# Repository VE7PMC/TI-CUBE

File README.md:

# The TI CUBE

The `TI CUBE` is an open-source homebrew microcomputer project I designed around the Texas Instruments TMS 9900 microprocessor and its associated peripheral devices.

In its basic form the `TI CUBE` supports communications through two serial ports and has 32 KiB of ROM and 32 KiB of RAM for code and data storage. It also supports FM sound playback using the YM3812 OPL2 FM synthesis IC. **This even allows it to play Doom!**

\* of course it can't "play" Doom in the sense of rendering 3D video! [But it can *play back* the Doom music using the YM3812 FM synthesizer.](https://www.youtube.com/watch?v=pIbxxHVAydw)

# Why the TMS 9900?

The [TMS 9900 microprocessor was relatively advanced for its time (released in 1976)](https://www.cpushack.com/2015/02/05/ti-tms9900sbp9900-accidental-success/) and is essentially a single-chip version of TI's 990 series of 16-bit minicomputers from the 1970s. The TMS 9900 is considered one of the first true 16-bit microprocessors with a full 16-bit external data bus. This was allowed by the use of rather unconventional 64-pin DIP package. The address bus uses 15 bits, but since all memory accesses are 16-bits wide, this provides a 64 KiB address space (32 K of 16 bit words). The most unique feature of the TMS 9900 is that it had no internal registers, other than the program counter (PC), workspace pointer (WP), and status register (SR) - all 16-bits wide. Instead of internal registers, the WP pointed to a region in external memory where 16 "registers" were stored in sequential memory addresses. Adjusting the WP allowed for very fast context switching by pointing to a different set of "registers". This capability was used in TI 990 minicomputers to support multiuser computing.

The elegance of the internal AND external 16-bit data bus (unlike the crippled Intel 8088 CPU used in the first IBM PC), the quirkiness of its memory-based registers, and its unique serial-based I/O CRU interface make this chip a fascinating way to explore early microcomputer technology and its capabilities.

Finally, the project was greatly inspired by [Usagi Electric](https://www.youtube.com/@UsagiElectric)'s ongoing homebrew computer project based on the TMS 9900 CPU. I had a spare TMS 9900 IC that I removed from a TI-99/4A several decades ago(!), and figured this was a good way to put it to use. 

# Design Philosophy

The following principles guided my development of this homebrew project. The list is roughly in order of priority (highest is first).

1. **No 8-bit data buses!** The TMS 9900 microprocessor is fundamentally a 16-bit design descendent from TI's 990 series of 16-bit minicomputers and I wanted to honour this ancestry as much as possible. I find address/data bus muxing/demuxing complex and inelegant. Yes, the TMS 9900 isn't the fastest of the TMS 99xx series of microprocessors, but it's the only one that supports an *external* 16-bit data bus interface.

2. **Modularity.** Just like a minicomputer which would typically have a backplane populated with multiple cards, the `TI CUBE` uses a similar philosophy with three basic cards: 
   * CPU card (with clock and interrupt control)
   * Memory card (holding the RAM and ROM)
   * Serial port interface card (equipped with two serial chips driving two EIA-232C compatible ports). 
  
   All cards plug into a backplane using 72-pin header connectors. Any card can go in any slot, and multiple cards (e.g., multiple serial interface cards) are supported. Additional backplanes can also be daisy-chained to support additional card slots.

3. **Board size.** Constraining the board size to 100 x 100 mm (4 x 4 in) allows ordering PCBs using the [JLCPCB](https://jlcpcb.com) or [PCBWAY](https://pcbway.com) prototyping services (personally, I have had great experience with JLCPCB). This significantly reduces the cost of individual boards (approximately $2 per board). The physical construction also gives the `TI CUBE` its name: four 100 x 100 mm vertical cards plugged into a horizontal four-slot 100 x 100 mm backplane.

   Interestingly, these dimensions are similar to those used by [CubeSat](https://en.wikipedia.org/wiki/CubeSat) modules. Perhaps a `TI CUBE` will someday get launched into orbit as the most underpowered satellite ever.

5. **Simplicity.** I subscribe to the [Earl Muntz](https://en.wikipedia.org/wiki/Muntzing) philosophy. As such, the `TI CUBE` design uses the minimum required amount of components to accomplish its function. Random logic (i.e., TTL gates and decoders) is complex and consumes significant board space. Instead, I prefer to use simple and standard PLD devices like the ubiquitous 16V8, which does everything needed in one chip. This also allows easily reconfigurability simply by reprogramming the PLD.

   There are  no address or data buffers in the `TI CUBE`, but the small size combined with the use of four-layer PCBs keeps the digital signals clean; my builds have demonstrated excellent reliablity and performance. 

6. **Period correctness.** Primarily this means use of only through-hole components and no surface mount devices (SMD). I don't mind SMD as such, but through-hole is still easier to assemble and is more consistent with 70s/80s computers. I have violated the period-correctness rule in number of other places (e.g., use of PLDs instead of random logic, larger memory ICs compared to what was available in the 70s and early 80s), so this one is more a [guideline than an actual rule](https://www.youtube.com/watch?v=omjnIeLIzJc&t=13s). 😉

7. **Use of TMS 9900 family peripherals.** The TMS 9900 has a unique serial-oriented I/O bus: the "CRU" (communications-register unit). While there is a plethora of external I/O devices that could be memory mapped, I wanted the `TI CUBE` to remain consistent with the TMS 9900 ecosystem through the used of CRU-based I/O where possible. Currently, this includes the TMS 9901 programmable systems interface (PSI) and the TMS 9902 asynchronous communications controller (ACC). 
   
8. **Compatibility.** I designed the `TI CUBE` to be generally compatible with other TMS 9900-based systems. One excellent example is [Stuart Connor's TMS 9900 breadboard/PCB system](http://www.stuartconner.me.uk/tms9900_breadboard/tms9900_breadboard.htm). In fact, the binary files he provides can be downloaded, burned to EPROMs, and used directly in the `TI CUBE`. This includes the TIBUG and EVMBUG monitors and Cortex BASIC which work right out of the box!

# Folders

## [KiCad/](KiCad/README.md)

The complete schematic and PCB design files in KiCad format. The schematics are also available in PDF format.

## [PLD configs/](PLD%20configs/README.md)

Files containing the address decoding logic for the various peripherals.

## [firmware/](firmware/README.md)

Binary files developed by Stuart Connor ready for burning to EPROMs. These contain TIBUG, EVMBUG, and Cortext BASIC.

## [hardware/](hardware/README.md)

The bill of materials and suggestions for acquiring the necessary components.

## [gerbers/](gerbers/README.md)

PCB design files ready for uploaded to your favourite PCB manufacturing house.

# Future Expansion/Ideas

This [file](FUTURE.md) contains my current thoughts on future expansions and/or design modifications.

# References

* [TI 9900 Family Systems Design and Data Book](https://www.bitsavers.org/components/ti/TMS9900/1978_TI_9900_Family_Systems_Design_and_Data_Book_1ed.pdf)
* [TMS 9900 Microprocessor Data Manual](https://datasheets.chipdb.org/TI/9900/TMS9900_DataManual.pdf)
* [The TI-99/4A Tech Pages](https://www.unige.ch/medecine/nouspikel/ti99/titechpages.htm)
* [TI TMS9900/SBP9900: Accidental Success](https://www.cpushack.com/2015/02/05/ti-tms9900sbp9900-accidental-success/)
* [The Inside Story of Texas Instruments’ Biggest Blunder: The TMS9900 Microprocessor](https://spectrum.ieee.org/the-inside-story-of-texas-instruments-biggest-blunder-the-tms9900-microprocessor)

# Acknowledgements

The following are excellent resources from other experimenters with the TMS 9900:

* [Usagi Electric's](https://www.youtube.com/@UsagiElectric) awesome YouTube channel.
* [Stuart Conner's Home Page](http://www.stuartconner.me.uk/) contains very helpful hardware designs and software files which I have referenced in the `TI CUBE` design.
* [POWERTRAN Cortex](http://powertrancortex.com/index.html) contains source code for Cortex BASIC which can be modified to run on the `TI CUBE`.

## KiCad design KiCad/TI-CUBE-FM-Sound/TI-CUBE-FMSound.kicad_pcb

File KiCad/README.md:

# TI Cube schematics and PCB design files

These folders contain the schematic and PCB design files for the four boards and backplane in KiCad 9.0.7 format.

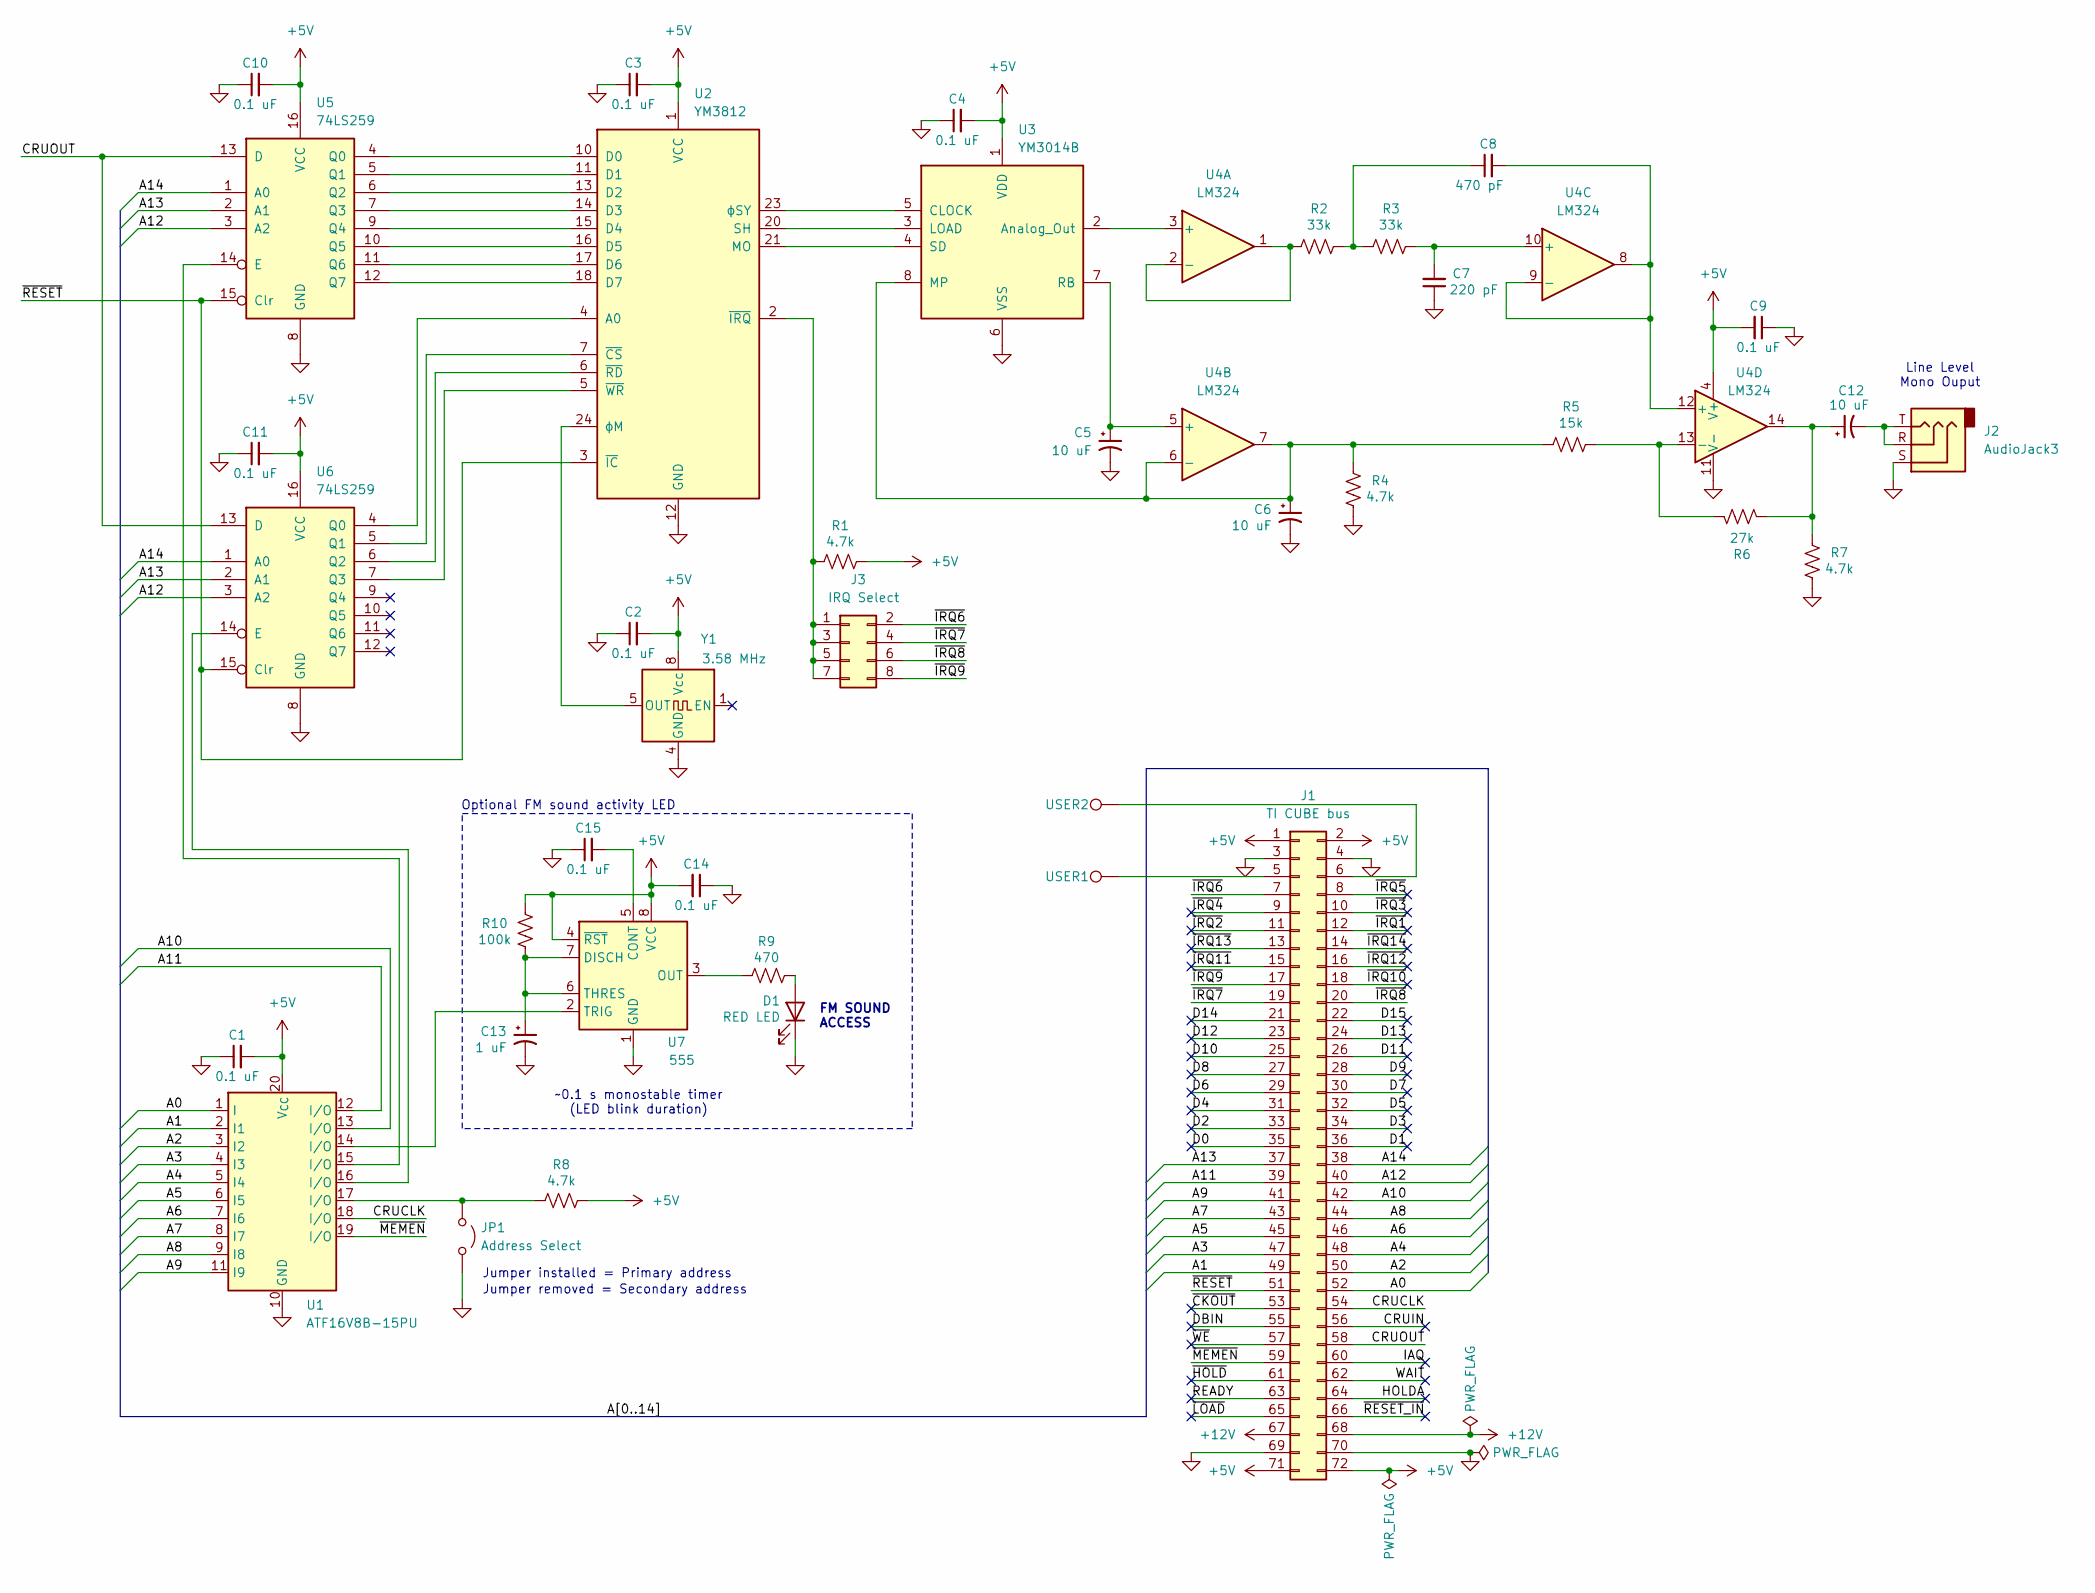
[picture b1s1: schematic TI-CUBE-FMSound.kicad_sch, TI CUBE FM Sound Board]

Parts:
C1, C2, C3, C4, C9, C10, C11, C14, C15: 0.1 uF; C_Ceramic_Cap_P2.50mm
C5, C6, C12: 10 uF; CP_Radial_D5.0mm_P2.50mm
C7: 220 pF; C_Ceramic_Cap_P2.50mm
C8: 470 pF; C_Ceramic_Cap_P2.50mm
C13: 1 uF; CP_Radial_D5.0mm_P2.50mm
D1: RED LED; LED_D3.0mm_Horizontal_O1.27mm_Z2.0mm
J1: TI CUBE bus; PinHeader_2x36_P2.54mm_Horizontal
J2: AudioJack3; Jack_3.5mm_CUI_SJ1-3513N_Horizontal
J3: IRQ Select; PinHeader_2x04_P2.54mm_Vertical
JP1: Address Select; PinHeader_1x02_P2.54mm_Vertical
R1, R4, R7, R8: 4.7k; R_Axial_DIN0207_L6.3mm_D2.5mm_P10.16mm_Horizontal
R2, R3: 33k; R_Axial_DIN0207_L6.3mm_D2.5mm_P10.16mm_Horizontal
R5: 15k; R_Axial_DIN0207_L6.3mm_D2.5mm_P10.16mm_Horizontal
R6: 27k; R_Axial_DIN0207_L6.3mm_D2.5mm_P10.16mm_Horizontal
R9: 470; R_Axial_DIN0207_L6.3mm_D2.5mm_P10.16mm_Horizontal
R10: 100k; R_Axial_DIN0207_L6.3mm_D2.5mm_P10.16mm_Horizontal
U1: ATF16V8B-15PU; DIP-20_W7.62mm
U2: YM3812; DIP-24_W15.24mm
U3: YM3014B; DIP-8_W7.62mm
U4: LM324; DIP-14_W7.62mm
U5, U6: 74LS259; DIP-16_W7.62mm
U7: 555; DIP-8_W7.62mm
USER1: USER1; TestPoint_THTPad_D1.5mm_Drill0.7mm
USER2: USER2; TestPoint_THTPad_D1.5mm_Drill0.7mm
Y1: 3.58 MHz; Oscillator_DIP-8

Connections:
+5V: C1.2, C2.2, C3.2, C4.2, C9.2, C10.2, C11.2, C14.2, J1.1, J1.2, J1.71, J1.72, R1.1, R8.1, R10.1, U1.20 (V_{CC}), U2.1 (VCC), U3.1 (VDD), U4.4 (V+), U5.16 (VCC), U6.16 (VCC), U7.4 (~RST), U7.8 (VCC), Y1.8 (Vcc)
+12V: J1.67, J1.68
/A0: J1.52, U1.1 (I)
/A1: J1.49, U1.2 (I1)
/A2: J1.50, U1.3 (I2)
/A3: J1.47, U1.4 (I3)
/A4: J1.48, U1.5 (I4)
/A5: J1.45, U1.6 (I5)
/A6: J1.46, U1.7 (I6)
/A7: J1.43, U1.8 (I7)
/A8: J1.44, U1.9 (I8)
/A9: J1.41, U1.11 (I9)
/A10: J1.42, U1.13 (I/O)
/A11: J1.39, U1.12 (I/O)
/A12: J1.40, U5.3 (A2), U6.3 (A2)
/A13: J1.37, U5.2 (A1), U6.2 (A1)
/A14: J1.38, U5.1 (A0), U6.1 (A0)
/CRUCLK: J1.54, U1.18 (I/O)
/CRUIN: J1.56
/CRUOUT: J1.58, U5.13 (D), U6.13 (D)
/D0: J1.35
/D1: J1.36
/D2: J1.33
/D3: J1.34
/D4: J1.31
/D5: J1.32
/D6: J1.29
/D7: J1.30
/D8: J1.27
/D9: J1.28
/D10: J1.25
/D11: J1.26
/D12: J1.23
/D13: J1.24
/D14: J1.21
/D15: J1.22
/DBIN: J1.55
/HOLDA: J1.64
/IAQ: J1.60
/READY: J1.63
/WAIT: J1.62
/~CKOUT: J1.53
/~HOLD: J1.61
/~IRQ1: J1.12
/~IRQ2: J1.11
/~IRQ3: J1.10
/~IRQ4: J1.9
/~IRQ5: J1.8
/~IRQ6: J1.7, J3.2
/~IRQ7: J1.19, J3.4
/~IRQ8: J1.20, J3.6
/~IRQ9: J1.17, J3.8
/~IRQ10: J1.18
/~IRQ11: J1.15
/~IRQ12: J1.16
/~IRQ13: J1.13
/~IRQ14: J1.14
/~LOAD: J1.65
/~MEMEN: J1.59, U1.19 (I/O)
/~RESET_IN: J1.66
/~RESET: J1.51, U2.3 (~IC), U5.15 (Clr), U6.15 (Clr)
/~WE: J1.57
GND: C1.1, C2.1, C3.1, C4.1, C5.2, C6.2, C7.1, C9.1, C10.1, C11.1, C13.2, C14.1, C15.1, D1.1 (K), J1.3, J1.4, J1.69, J1.70, J2.S, JP1.2 (B), R4.1, R7.1, U1.10 (GND), U2.12 (GND), U3.6 (VSS), U4.11 (V-), U5.8 (GND), U6.8 (GND), U7.1 (GND), Y1.4 (GND)
unnamed: C8.1, R2.1, R3.2
unnamed: C12.1, R6.1, R7.2, U4.14
unnamed: C12.2, J2.R, J2.T
unnamed: D1.2 (A), R9.1
unnamed: J1.5, USER1.1
unnamed: J1.6, USER2.1
unnamed: J3.1, J3.3, J3.5, J3.7, R1.2, U2.2 (~IRQ)
unnamed: JP1.1 (A), R8.2, U1.17 (I/O)
unnamed: U2.4 (A0), U6.4 (Q0)
unnamed: U2.10 (D0), U5.4 (Q0)
unnamed: U2.11 (D1), U5.5 (Q1)
unnamed: U2.13 (D2), U5.6 (Q2)
unnamed: U2.14 (D3), U5.7 (Q3)
unnamed: U2.15 (D4), U5.9 (Q4)
unnamed: U2.16 (D5), U5.10 (Q5)
unnamed: U2.17 (D6), U5.11 (Q6)
unnamed: U2.18 (D7), U5.12 (Q7)
unnamed: U2.21 (MO), U3.4 (SD)
unnamed: U2.20 (SH), U3.3 (LOAD)
unnamed: U2.7 (~CS), U6.5 (Q1)
unnamed: U2.6 (~RD), U6.6 (Q2)
unnamed: U2.5 (~WR), U6.7 (Q3)
unnamed: U2.24 (ϕM), Y1.5 (OUT)
unnamed: U2.23 (ϕSY), U3.5 (CLOCK)
unnamed: U3.2 (Analog_Out), U4.3 (+)
unnamed: C6.1, R4.2, R5.2, U3.8 (MP), U4.6 (-), U4.7
unnamed: C5.1, U3.7 (RB), U4.5 (+)
unnamed: R2.2, U4.1, U4.2 (-)
unnamed: C7.2, R3.1, U4.10 (+)
unnamed: C8.2, U4.8, U4.9 (-), U4.12 (+)
unnamed: R5.1, R6.2, U4.13 (-)
unnamed: U1.15 (I/O), U5.14 (E)
unnamed: U1.16 (I/O), U6.14 (E)
unnamed: C15.2, U7.5 (CONT)
unnamed: C13.1, R10.2, U7.6 (THRES), U7.7 (DISCH)
unnamed: R9.2, U7.3 (OUT)
unnamed: U1.14 (I/O), U7.2 (TRIG)

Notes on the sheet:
Line Level Mono Ouput
Optional FM sound activity LED
Jumper removed = Secondary address
FM SOUND ACCESS
~0.1 s monostable timer (LED blink duration)
Jumper installed = Primary address

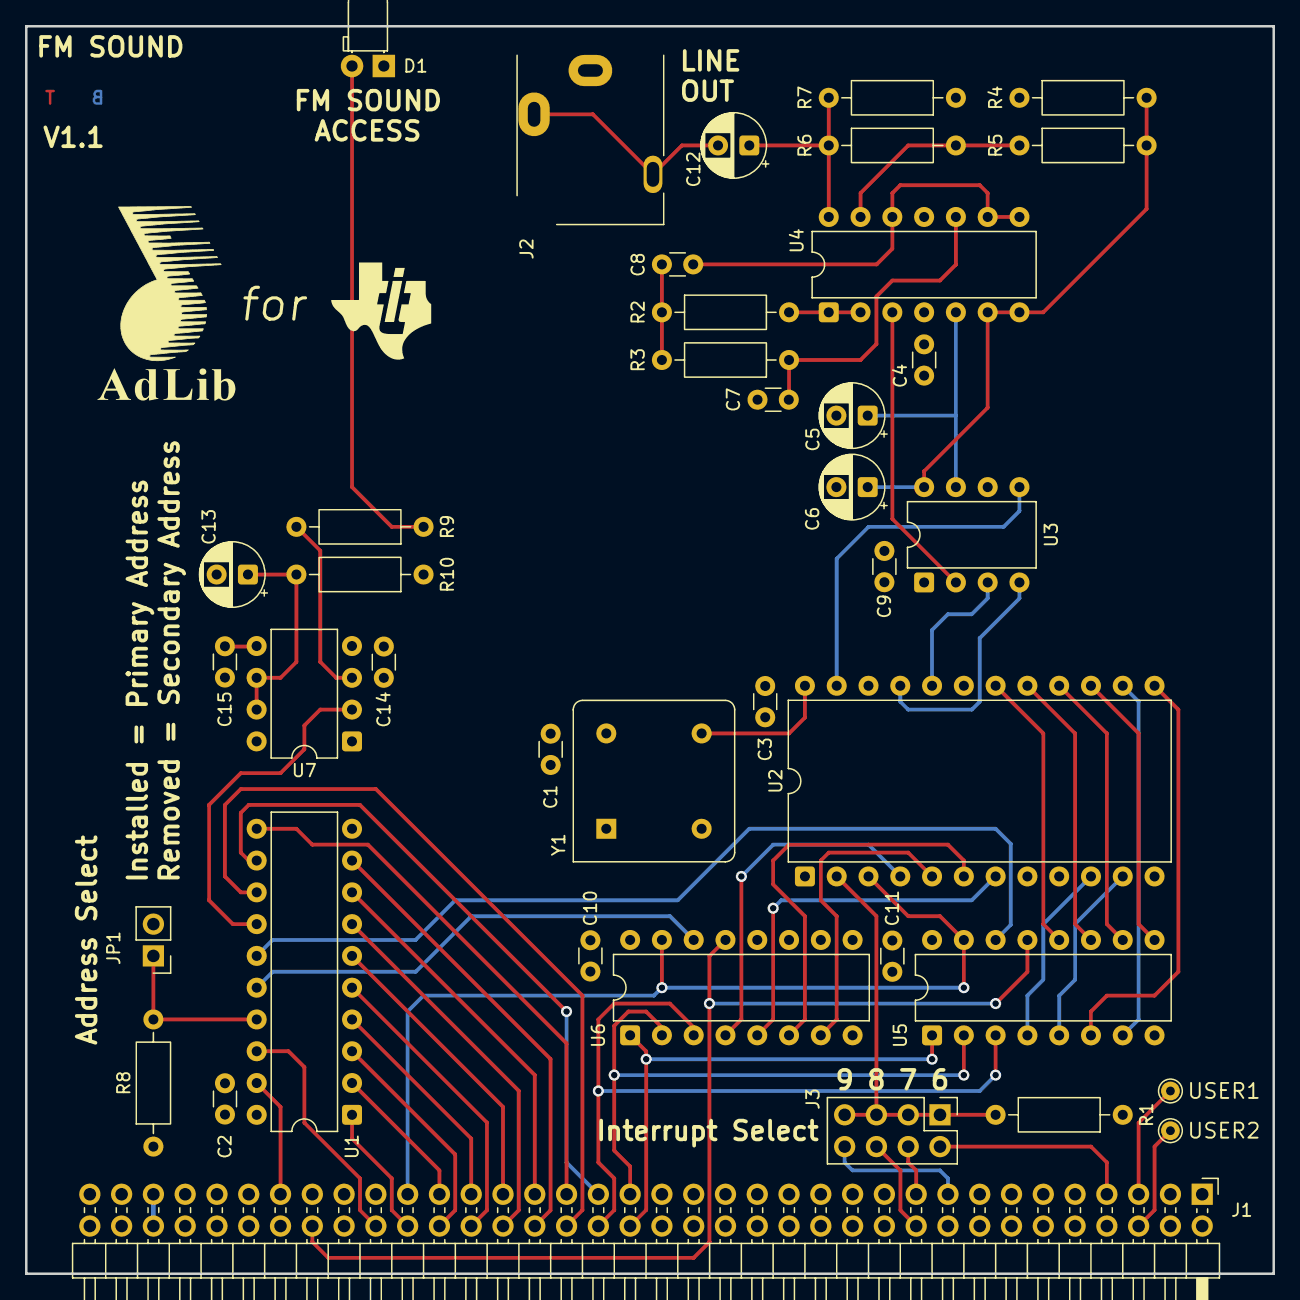
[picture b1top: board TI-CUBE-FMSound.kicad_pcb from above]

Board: 4 copper layers, 99.7 x 99.7 mm, 40 parts (0 on the bottom side), 63 nets.

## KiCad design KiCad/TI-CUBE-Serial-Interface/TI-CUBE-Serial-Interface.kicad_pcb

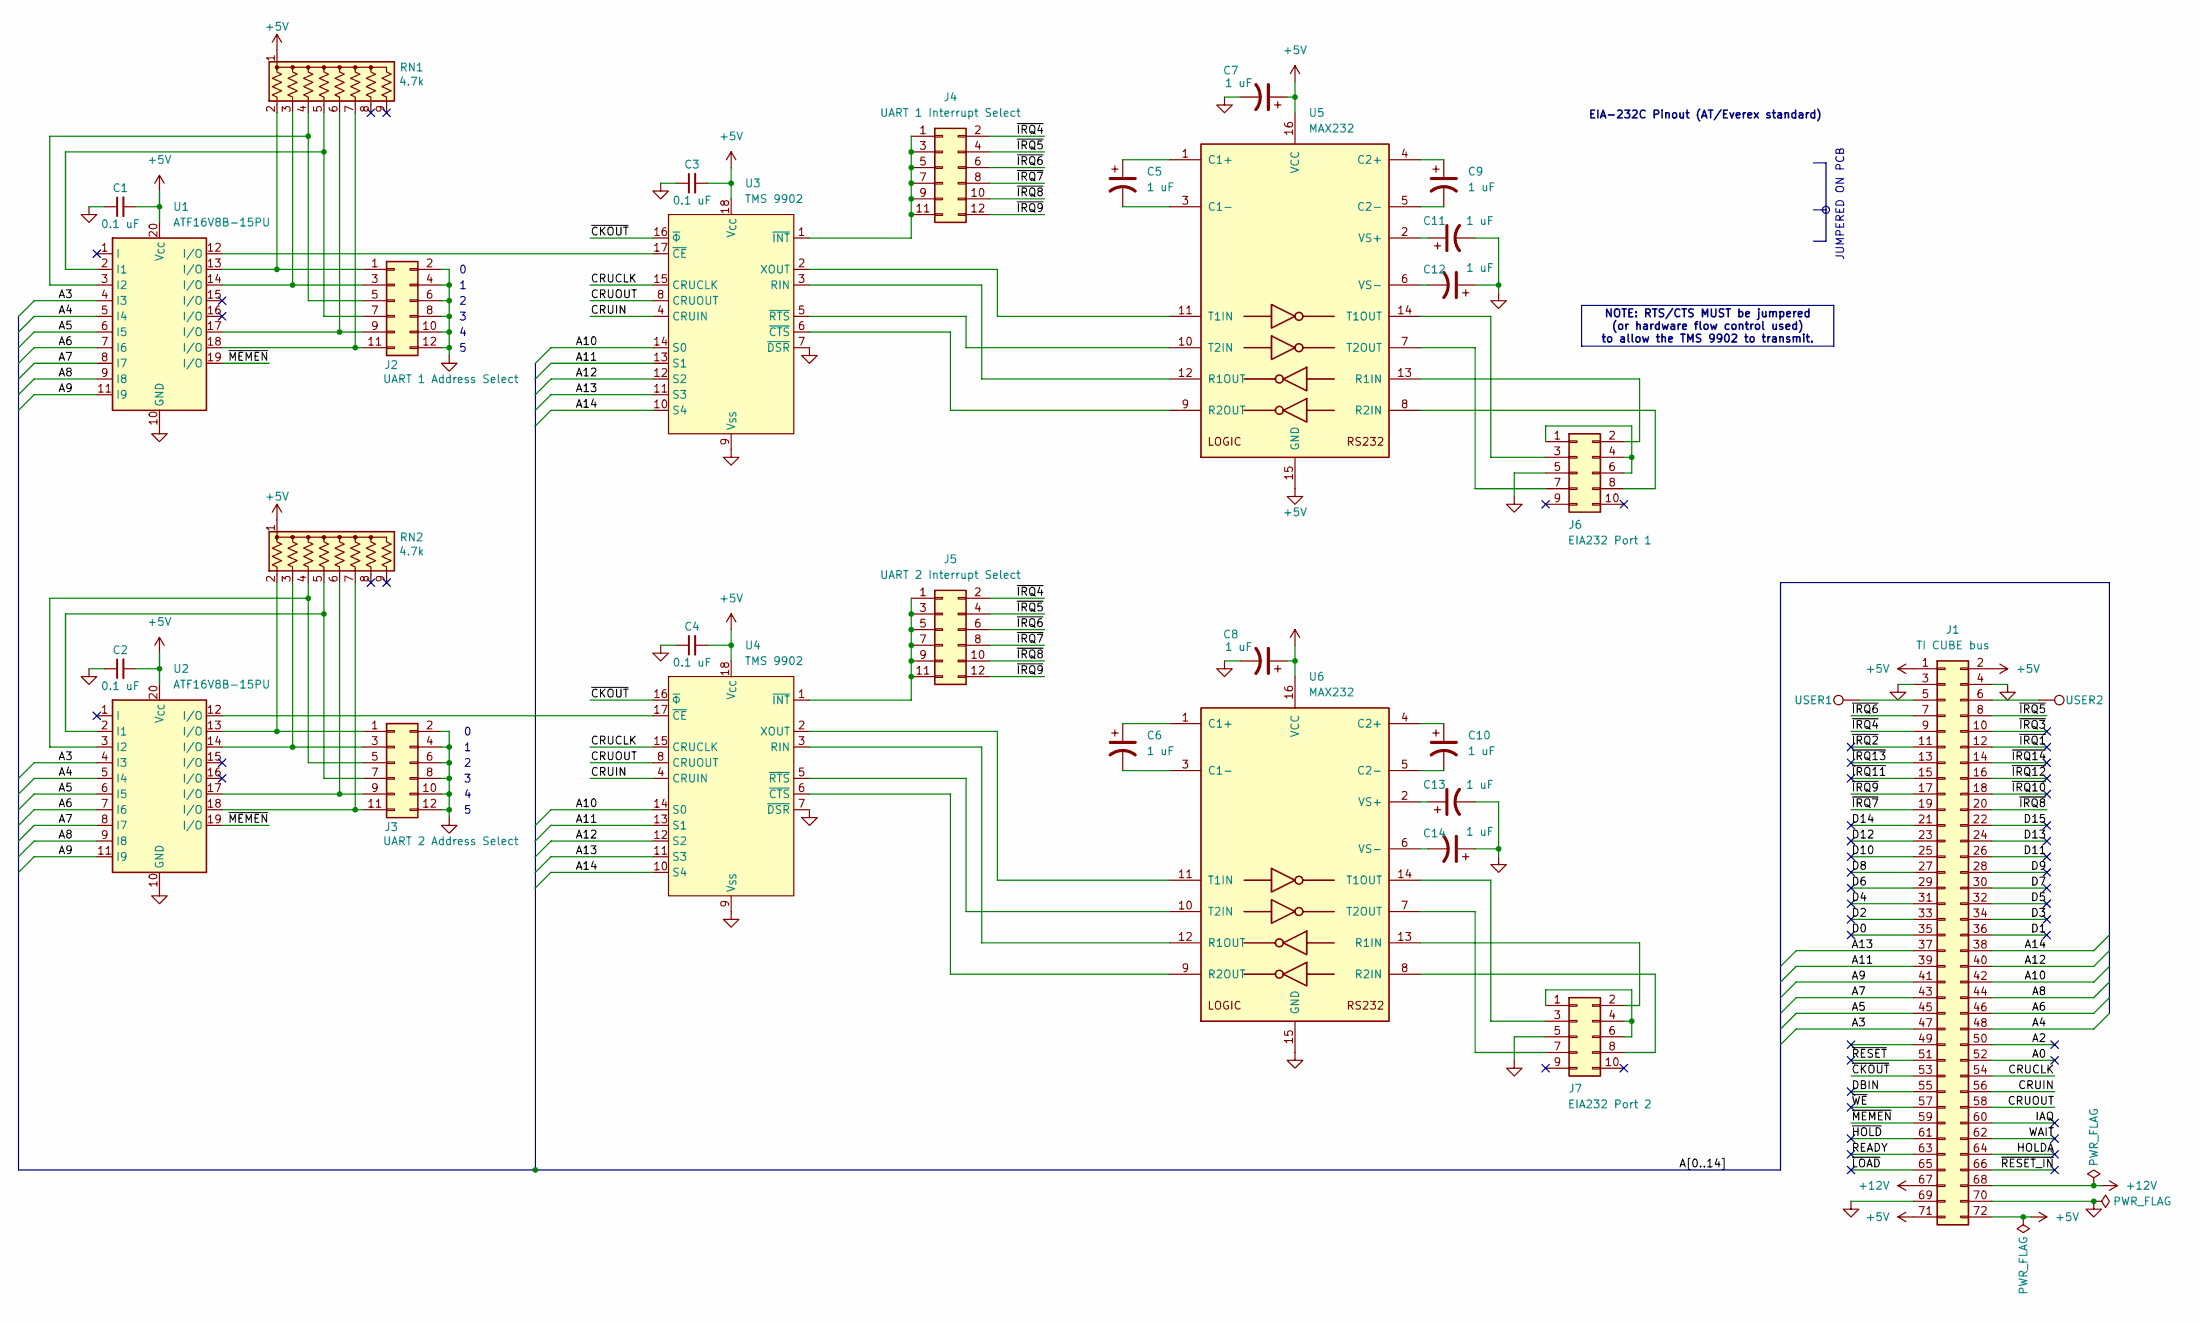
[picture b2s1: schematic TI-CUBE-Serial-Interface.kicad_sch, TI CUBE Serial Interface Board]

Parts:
C1, C2, C3, C4: 0.1 uF; C_Ceramic_Cap_P2.50mm
C5, C6, C7, C8, C9, C10, C11, C12, C13, C14: 1 uF; CP_Radial_D5.0mm_P2.50mm
J1: TI CUBE bus; PinHeader_2x36_P2.54mm_Horizontal
J2: UART 1 Address Select; PinHeader_2x06_P2.54mm_Vertical
J3: UART 2 Address Select; PinHeader_2x06_P2.54mm_Vertical
J4: UART 1 Interrupt Select; PinHeader_2x06_P2.54mm_Vertical
J5: UART 2 Interrupt Select; PinHeader_2x06_P2.54mm_Vertical
J6: EIA232 Port 1; PinHeader_2x05_P2.54mm_Horizontal
J7: EIA232 Port 2; PinHeader_2x05_P2.54mm_Horizontal
RN1, RN2: 4.7k; R_Array_SIP9
U1, U2: ATF16V8B-15PU; DIP-20_W7.62mm
U3, U4: TMS 9902; DIP-18_W7.62mm
U5, U6: MAX232; DIP-16_W7.62mm
USER1: USER2; TestPoint_THTPad_D1.5mm_Drill0.7mm
USER2: USER1; TestPoint_THTPad_D1.5mm_Drill0.7mm

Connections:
+5V: C1.2, C2.2, C3.2, C4.2, C7.1, C8.1, J1.1, J1.2, J1.71, J1.72, RN1.1 (common), RN2.1 (common), U1.20 (V_{CC}), U2.20 (V_{CC}), U3.18 (V_{CC}), U4.18 (V_{CC}), U5.16 (VCC), U6.16 (VCC)
+12V: J1.67, J1.68
/A0: J1.52
/A2: J1.50
/A3: J1.47, U1.4 (I3), U2.4 (I3)
/A4: J1.48, U1.5 (I4), U2.5 (I4)
/A5: J1.45, U1.6 (I5), U2.6 (I5)
/A6: J1.46, U1.7 (I6), U2.7 (I6)
/A7: J1.43, U1.8 (I7), U2.8 (I7)
/A8: J1.44, U1.9 (I8), U2.9 (I8)
/A9: J1.41, U1.11 (I9), U2.11 (I9)
/A10: J1.42, U3.14 (S0), U4.14 (S0)
/A11: J1.39, U3.13 (S1), U4.13 (S1)
/A12: J1.40, U3.12 (S2), U4.12 (S2)
/A13: J1.37, U3.11 (S3), U4.11 (S3)
/A14: J1.38, U3.10 (S4), U4.10 (S4)
/CRUCLK: J1.54, U3.15 (CRUCLK), U4.15 (CRUCLK)
/CRUIN: J1.56, U3.4 (CRUIN), U4.4 (CRUIN)
/CRUOUT: J1.58, U3.8 (CRUOUT), U4.8 (CRUOUT)
/D0: J1.35
/D1: J1.36
/D2: J1.33
/D3: J1.34
/D4: J1.31
/D5: J1.32
/D6: J1.29
/D7: J1.30
/D8: J1.27
/D9: J1.28
/D10: J1.25
/D11: J1.26
/D12: J1.23
/D13: J1.24
/D14: J1.21
/D15: J1.22
/DBIN: J1.55
/HOLDA: J1.64
/IAQ: J1.60
/READY: J1.63
/WAIT: J1.62
/~CKOUT: J1.53, U3.16 (~Φ), U4.16 (~Φ)
/~HOLD: J1.61
/~IRQ1: J1.12
/~IRQ2: J1.11
/~IRQ3: J1.10
/~IRQ4: J1.9, J4.2, J5.2
/~IRQ5: J1.8, J4.4, J5.4
/~IRQ6: J1.7, J4.6, J5.6
/~IRQ7: J1.19, J4.8, J5.8
/~IRQ8: J1.20, J4.10, J5.10
/~IRQ9: J1.17, J4.12, J5.12
/~IRQ10: J1.18
/~IRQ11: J1.15
/~IRQ12: J1.16
/~IRQ13: J1.13
/~IRQ14: J1.14
/~LOAD: J1.65
/~MEMEN: J1.59, U1.19 (I/O), U2.19 (I/O)
/~RESET_IN: J1.66
/~RESET: J1.51
/~WE: J1.57
GND: C1.1, C2.1, C3.1, C4.1, C7.2, C8.2, C11.2, C12.1, C13.2, C14.1, J1.3, J1.4, J1.69, J1.70, J2.2, J2.4, J2.6, J2.8, J2.10, J2.12, J3.2, J3.4, J3.6, J3.8, J3.10, J3.12, J6.5, J7.5, U1.10 (GND), U2.10 (GND), U3.7 (~DSR), U3.9 (V_{SS}), U4.7 (~DSR), U4.9 (V_{SS}), U5.15 (GND), U6.15 (GND)
unnamed: J1.5, USER2.1
unnamed: J1.6, USER1.1
unnamed: J2.1, RN1.2 (R1), U1.13 (I/O)
unnamed: J2.3, RN1.3 (R2), U1.14 (I/O)
unnamed: J2.5, RN1.4 (R3), U1.3 (I2)
unnamed: J2.7, RN1.5 (R4), U1.2 (I1)
unnamed: J2.9, RN1.6 (R5), U1.17 (I/O)
unnamed: J2.11, RN1.7 (R6), U1.18 (I/O)
unnamed: J3.1, RN2.2 (R1), U2.13 (I/O)
unnamed: J3.3, RN2.3 (R2), U2.14 (I/O)
unnamed: J3.5, RN2.4 (R3), U2.3 (I2)
unnamed: J3.7, RN2.5 (R4), U2.2 (I1)
unnamed: J3.9, RN2.6 (R5), U2.17 (I/O)
unnamed: J3.11, RN2.7 (R6), U2.18 (I/O)
unnamed: J4.1, J4.3, J4.5, J4.7, J4.9, J4.11, U3.1 (~INT)
unnamed: J5.1, J5.3, J5.5, J5.7, J5.9, J5.11, U4.1 (~INT)
unnamed: J6.1, J6.4, J6.6
unnamed: J6.2, U5.13 (R1IN)
unnamed: J6.3, U5.14 (T1OUT)
unnamed: J6.7, U5.7 (T2OUT)
unnamed: J6.8, U5.8 (R2IN)
unnamed: J7.1, J7.4, J7.6
unnamed: J7.2, U6.13 (R1IN)
unnamed: J7.3, U6.14 (T1OUT)
unnamed: J7.7, U6.7 (T2OUT)
unnamed: J7.8, U6.8 (R2IN)
unnamed: U3.3 (RIN), U5.12 (R1OUT)
unnamed: U3.2 (XOUT), U5.11 (T1IN)
unnamed: U1.12 (I/O), U3.17 (~CE)
unnamed: U3.6 (~CTS), U5.9 (R2OUT)
unnamed: U3.5 (~RTS), U5.10 (T2IN)
unnamed: U4.3 (RIN), U6.12 (R1OUT)
unnamed: U4.2 (XOUT), U6.11 (T1IN)
unnamed: U2.12 (I/O), U4.17 (~CE)
unnamed: U4.6 (~CTS), U6.9 (R2OUT)
unnamed: U4.5 (~RTS), U6.10 (T2IN)
unnamed: C5.1, U5.1 (C1+)
unnamed: C5.2, U5.3 (C1-)
unnamed: C9.1, U5.4 (C2+)
unnamed: C9.2, U5.5 (C2-)
unnamed: C11.1, U5.2 (VS+)
unnamed: C12.2, U5.6 (VS-)
unnamed: C6.1, U6.1 (C1+)
unnamed: C6.2, U6.3 (C1-)
unnamed: C10.1, U6.4 (C2+)
unnamed: C10.2, U6.5 (C2-)
unnamed: C13.1, U6.2 (VS+)
unnamed: C14.2, U6.6 (VS-)

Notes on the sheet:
JUMPERED ON PCB
EIA-232C Pinout (AT/Everex standard)
NOTE: RTS/CTS MUST be jumpered (or hardware flow control used) to allow the TMS 9902 to transmit.

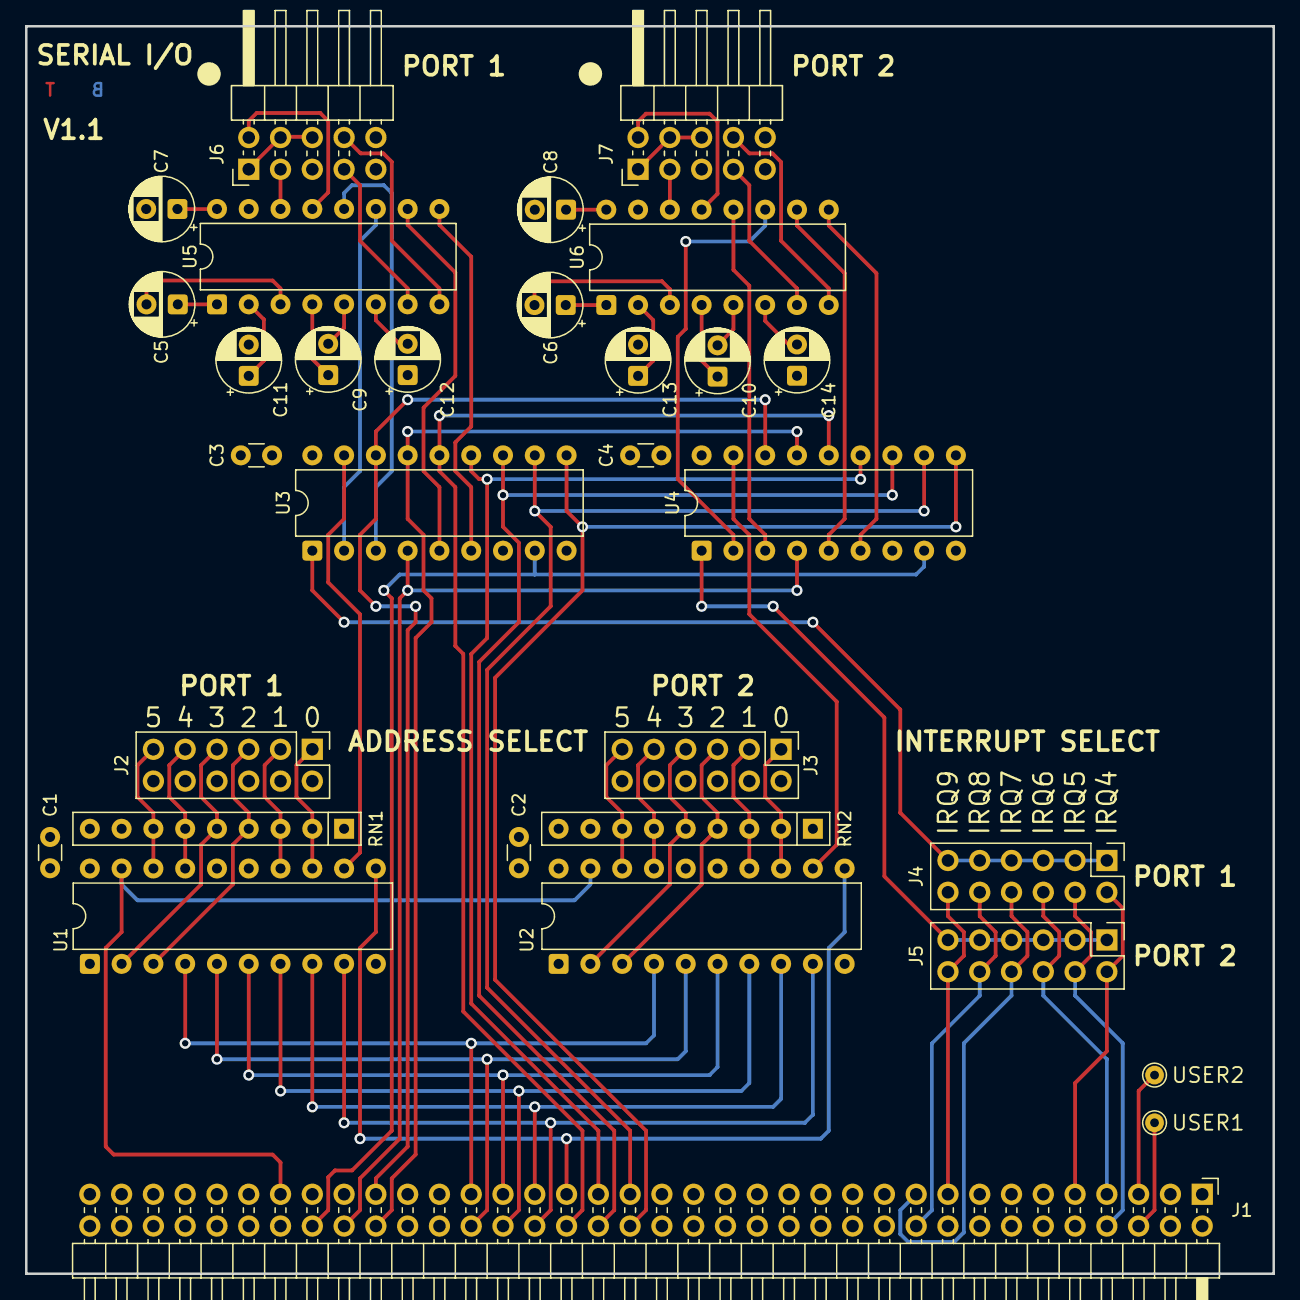
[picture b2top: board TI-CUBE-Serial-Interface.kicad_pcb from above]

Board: 4 copper layers, 99.7 x 99.7 mm, 31 parts (0 on the bottom side), 74 nets.

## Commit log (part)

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2026-03-02 Restore README.md content with formatting corrections
    Fixed footnotes.
2026-03-02 Update README with additional specifications and details
2026-03-07 Fix formatting issues in README.md
2026-03-07 Renamed KiCad folder
2026-03-07 Fix links to EPROM files in README.md
2026-03-22 Create CNAME
2026-04-05 Update RAM Memory Expansion section in README
    Clarify the advantages of RAM expansion for the TI CUBE and mention Stuart Conner's contributions.
2026-04-05 Update README with project details and specifications
    Updated the detailed project description, design philosophy, hardware specifications, and future expansion ideas for the TI CUBE microcomputer.
2026-04-05 Enhance README with TMS 9900 family details
    Updated README to include detailed component descriptions for TMS 9900 family.
2026-04-05 Renamed folder
2026-04-05 Fix typo in TMS 9901 description
2026-04-05 Update README to use 'boards' instead of 'cards'
2026-04-05 Revise README with project details and specifications
    Updated the README to include additional details about the TI CUBE project, design philosophy, hardware specifications, and future expansion ideas.
2026-04-05 Revise README structure and content
    Updated the README to improve clarity and organization.
2026-04-05 Add hardware specifications for TI CUBE
    Added detailed hardware specifications for TI CUBE, including CPU, memory, serial I/O, protoboard, and backplane components.
2026-04-05 Revise README.md content and formatting
2026-04-05 Remove note about PLD programmer requirement
    Removed a note about the necessity of a programmer for PLDs.
2026-04-05 Create FUTURE.md for expansion ideas on TI CUBE
    Added a new document outlining thoughts on future expansion and modifications for the TI CUBE, including external instructions, RAM memory expansion, and storage options.
2026-04-05 Updated to match revised pin assignments
2026-04-05 Restore README.md content after removal
2026-04-05 Updated to Rev 1.1 design.
2026-04-05 Add upload instructions for PCB manufacturing
2026-04-06 Fix image paths in gerbers README
    Updated image paths in README for Gerber files.
2026-04-06 Update README with additional PCB settings
    Added additional PCB settings section to README.
2026-04-06 Clarify description of Gerber files in README
    Updated the README to clarify the contents of the .zip files.
2026-04-06 Refactor TI 990 instructions section in FUTURE.md
    Reorganized and clarified descriptions of TI 990 instructions and their functions. Improved structure and readability of the document.
2026-04-06 Update README.md with project details and philosophy
2026-04-06 Update HARDWARE.md with expansion connector details
    Added information about expansion connectors and spare bus lines.
2026-04-06 Update README with PLD configuration details
    Added detailed descriptions and configurations for PLD files used in TI CUBE systems, including address decoding for TMS 9901 and TMS 9902 devices.
2026-04-06 Improve README with detailed PLD and programming info
    Updated README.md to enhance descriptions of PLDs and file formats.
2026-04-06 Update README.md with project details
2026-04-06 Update README with references and acknowledgements
    Added references and acknowledgements sections to README.
2026-04-06 Add 'Can it run Doom?' section to FUTURE.md
    Added a section discussing the feasibility of running Doom on the TI CUBE.
2026-04-07 Update README with hardware specs and future ideas
    Added additional details about hardware specifications, future expansion ideas, and references.
2026-04-07 Document TI CUBE hardware specifications
    Added detailed hardware specifications for TI CUBE components including CPU, memory, serial I/O, protoboard, and backplane.
2026-04-07 Restore and format README.md content
    Restored the README.md content and improved formatting.
2026-04-07 Update README with component ordering information
    Added component ordering information and BOM details.
2026-04-07 Update README with component ordering details
    Clarified component ordering information and updated details on sourcing parts.
2026-04-07 Deleted file.
2026-04-08 Update README with folder structure and acknowledgements
    Added sections on folders and acknowledgements for additional resources.
2026-04-08 Revise README.md with project overview and philosophy
    Updated the README.md to include project details and design philosophy.
2026-04-08 Renamed file.
2026-04-08 Update README with TI CUBE logo and project overview
    Added logo image and introductory text to README.
2026-04-09 Update README with project details and philosophy
2026-04-09 Update README with logo and project overview
    Added TI CUBE logo and introductory text to README
2026-04-09 Revise README with project details and resources
    Updated README.md to include project overview, design philosophy, folder structure, references, and acknowledgements.
2026-04-09 Add demo section for Cortex BASIC
    Added a demo section for running Cortex BASIC with an image.
2026-04-15 Enhance README with TIBUG demo and Cortex BASIC info
    Added a section for TIBUG demo
